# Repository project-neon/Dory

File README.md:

# Dory
3rd Sumo Robot for Project Neon. After Zumo and Nemo, comes Dory.

Repositório de desenvolvimento para a Dory em 2022.

Usamos o fluxo de trabalho apresentado [aqui pelo Gamen](https://github.com/project-neon/codestyleguide/blob/master/git.md). Também está apresentado no [github flow](https://docs.github.com/pt/get-started/quickstart/github-flow). O resumo seria este:

## Arquivos

  Neste repositório temos os principais arquivos que usamos para os 3 capítulos, Eletrônica, Mecânica e Software. Segue abaixo uma lista do que temos em cada uma das pastas:

  ### Electronics
    Na parte eletrônica, utilizamos o programa Kicad que é open source e permite a criação e edição de PCBs.
    Caso queira editar ou vizualizar o projeto, clone o diretório "Eletronics", pois nele está contido o esquemático 
    no formato PDF e sch,  a PCB no formato pcb e os arquivos pro e plr próprios do Kicad.
    
  ### Mechanics
    Na pasta da mecânica, há arquivos no formato step e stl para que possam ser utilizados para visualização 
    e manufatura 3D, juntamente com os arquivos pdf dos desenhos técnicos para melhor compreensão do projeto
    
  ### Software
    Nesta pasta deixamos todos os arquivos que formam o código do robô. Então .ino e .h são os principais arquivos.
    Usamos os .h's para segmentar o código e não ser um único bloco enorme, dividindo eles de acordo com sua funcionalidade.
    O .ino é onde fica a base de todo o código, como o setup() e o loop(). Temos os códigos de testes e o código autonomous
    que usamos durante as lutas oficiais.

## Fluxo Git
- Quando for acrescentar uma feature (um comportamento novo para o robô), crie uma brancha chamada `feat/nome-da-feature`
- Quando for corrir algum bug no código, crie uma brancha chamada `fix/nome-do-fix`
- Quando for adicionar novos arquivos na mecância ou eletrônica, crie uma brancha chamada `update/eletronics-<data>` ou `update/mechanis-<data>`, exemplo: `update/eletronics-01-04-2023`
- A partir da main: `git checkout -b nome-da-branch`, ex: `git checkout -b feat/novos-testes`

## Na hora de fazer o commit
- Nomeie o seu commit primeiro dizendo o que foi feito, ex: `fix: `, `feat: ` ou `update: `
- Você pode adicionar no assunto (comentário) ou na mensagem do commit também onde que a mudança foi feita.
- `git push`

Para saber mais de commits, você pode acessar esse [link](https://www.freecodecamp.org/news/how-to-write-better-git-commit-messages/)

## Na hora de fazer o merge
- Depois de subir o commit, crie um PR (Pull Request) e peça pro resto do pessoal da equipe dar uma conferida antes de ser aprovado

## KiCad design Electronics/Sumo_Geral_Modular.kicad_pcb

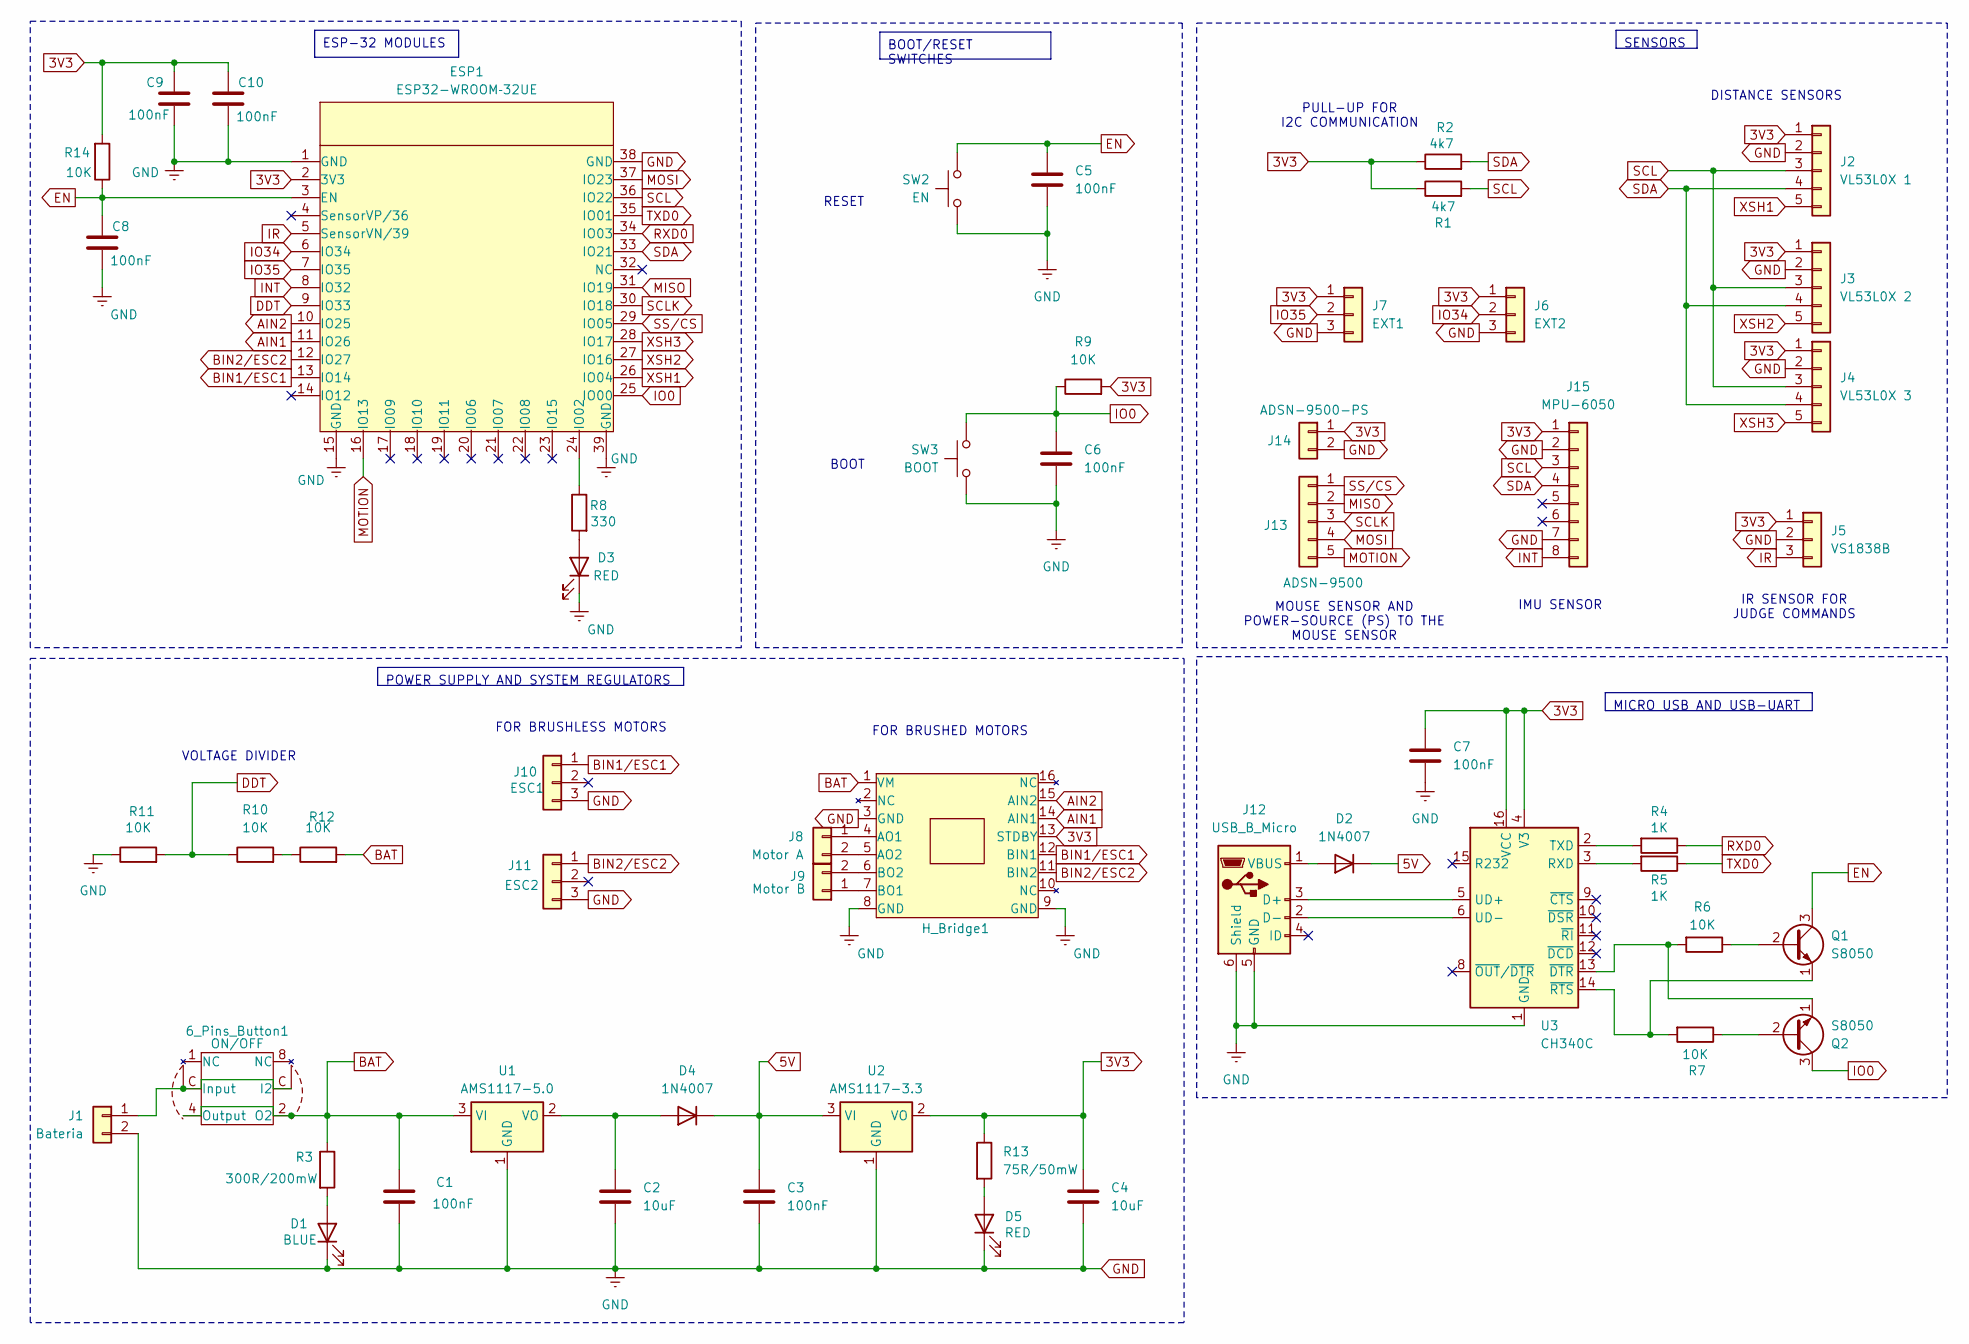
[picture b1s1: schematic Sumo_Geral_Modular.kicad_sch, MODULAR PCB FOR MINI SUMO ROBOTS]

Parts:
6_Pins_Button1: ON/OFF; Push_Button_6_pins
C1, C3, C5, C6, C7, C8, C9, C10: 100nF; C_0603_1608Metric
C2, C4: 10uF; C_0603_1608Metric
D1: BLUE; LED_0603_1608Metric
D2, D4: 1N4007; D_0603_1608Metric
D3, D5: RED; LED_0603_1608Metric
ESP1: ESP32-WROOM­32UE; ESP32-WROOM-32
H_Bridge1: H_Bridge_with_headers
J1: Bateria; JST_PH_B2B-PH-K_1x02_P2.00mm_Vertical
J2: VL53L0X 1; JST_XH_B5B-XH-A_1x05_P2.50mm_Vertical
J3: VL53L0X 2; JST_XH_B5B-XH-A_1x05_P2.50mm_Vertical
J4: VL53L0X 3; JST_XH_B5B-XH-A_1x05_P2.50mm_Vertical
J5: VS1838B; PinHeader_1x03_P2.00mm_Vertical
J6: EXT2; PinHeader_1x03_P2.00mm_Vertical
J7: EXT1; PinHeader_1x03_P2.00mm_Vertical
J8: Motor A; JST_XH_B2B-XH-A_1x02_P2.50mm_Vertical
J9: Motor B; JST_XH_B2B-XH-A_1x02_P2.50mm_Vertical
J10: ESC1; JST_XH_B3B-XH-A_1x03_P2.50mm_Vertical
J11: ESC2; JST_XH_B3B-XH-A_1x03_P2.50mm_Vertical
J12: USB_B_Micro; USB_Micro-B_Amphenol_10118194_Horizontal
J13: ADSN-9500; JST_XH_S5B-XH-A_1x05_P2.50mm_Horizontal
J14: ADSN-9500-PS; JST_XH_S2B-XH-A_1x02_P2.50mm_Horizontal
J15: MPU-6050; PinSocket_1x08_P2.54mm_Vertical
Q1, Q2: S8050; SOT-23
R1, R2: 4k7; R_0603_1608Metric
R3: 300R/200mW; R_0603_1608Metric
R4, R5: 1K; R_0603_1608Metric
R6, R7, R9, R11, R12, R14: 10K; R_0603_1608Metric
R8: 330; R_0603_1608Metric
R10: 10K; C_0603_1608Metric
R13: 75R/50mW; R_0603_1608Metric
SW2: EN; SW_SPST_TL3305C
SW3: BOOT; SW_SPST_TL3305C
U1: AMS1117-5.0; SOT-223-3_TabPin2
U2: AMS1117-3.3; SOT-223-3_TabPin2
U3: CH340C; SOIC-16_3.9x9.9mm_P1.27mm

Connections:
3V3: C4.1, C7.1, C9.1, C10.1, ESP1.2 (3V3), H_Bridge1.13 (STDBY), J2.1, J3.1, J4.1, J5.1, J6.1, J7.1, J14.1, J15.1, R1.1, R2.1, R9.2, R13.1, R14.2, U2.2 (VO), U3.4 (V3), U3.16 (VCC)
5V: C3.1, D2.1 (K), D4.1 (K), U2.3 (VI)
AIN1: ESP1.11 (IO26), H_Bridge1.14 (AIN1)
AIN2: ESP1.10 (IO25), H_Bridge1.15 (AIN2)
BAT: 6_Pins_Button1.2 (O2), 6_Pins_Button1.4 (Output), C1.1, H_Bridge1.1 (VM), R3.1, R12.2, U1.3 (VI)
BIN1/ESC1: ESP1.13 (IO14), H_Bridge1.12 (BIN1), J10.1
BIN2/ESC2: ESP1.12 (IO27), H_Bridge1.11 (BIN2), J11.1
DDT: ESP1.9 (IO33), R10.1, R11.2
EN: C5.2, C8.1, ESP1.3 (EN), Q1.3 (C), R14.1, SW2.1
GND: C1.2, C2.2, C3.2, C4.2, C5.1, C6.2, C7.2, C8.2, C9.2, C10.2, D1.1 (K), D3.1 (K), D5.1 (K), ESP1.1 (GND), ESP1.15 (GND), ESP1.38 (GND), ESP1.39 (GND), H_Bridge1.3 (GND), H_Bridge1.8 (GND), H_Bridge1.9 (GND), J1.2, J2.2, J3.2, J4.2, J5.2, J6.3, J7.3, J10.3, J11.3, J12.5 (GND), J12.6 (Shield), J14.2, J15.2, J15.7, R11.1, SW2.2, SW3.2, U1.1 (GND), U2.1 (GND), U3.1 (GND)
INT: ESP1.8 (IO32), J15.8
IO0: C6.1, ESP1.25 (IO00), Q2.3 (C), R9.1, SW3.1
IO34: ESP1.6 (IO34), J6.2
IO35: ESP1.7 (IO35), J7.2
IR: ESP1.5 (SensorVN/39), J5.3
MISO: ESP1.31 (IO19), J13.2
MOSI: ESP1.37 (IO23), J13.4
MOTION: ESP1.16 (IO13), J13.5
unnamed: 6_Pins_Button1.C (I2), J1.1
unnamed: D1.2 (A), R3.2
unnamed: D2.2 (A), J12.1 (VBUS)
unnamed: D3.2 (A), R8.2
unnamed: C2.1, D4.2 (A), U1.2 (VO)
unnamed: D5.2 (A), R13.2
unnamed: ESP1.24 (IO02), R8.1
unnamed: H_Bridge1.4 (AO1), J8.1
unnamed: H_Bridge1.5 (AO2), J8.2
unnamed: H_Bridge1.7 (BO1), J9.1
unnamed: H_Bridge1.6 (BO2), J9.2
unnamed: J12.3 (D+), U3.5 (UD+)
unnamed: J12.2 (D-), U3.6 (UD-)
unnamed: Q1.2 (B), R6.1
unnamed: Q1.1 (E), R7.2, U3.14 (~RTS)
unnamed: Q2.2 (B), R7.1
unnamed: Q2.1 (E), R6.2, U3.13 (~DTR)
unnamed: R10.2, R12.1
unnamed: R5.2, U3.3 (RXD)
unnamed: R4.2, U3.2 (TXD)
RXD0: ESP1.34 (IO03), R4.1
SCL: ESP1.36 (IO22), J2.3, J3.3, J4.3, J15.3, R1.2
SCLK: ESP1.30 (IO18), J13.3
SDA: ESP1.33 (IO21), J2.4, J3.4, J4.4, J15.4, R2.2
SS/CS: ESP1.29 (IO05), J13.1
TXD0: ESP1.35 (IO01), R5.1
XSH1: ESP1.26 (IO04), J2.5
XSH2: ESP1.27 (IO16), J3.5
XSH3: ESP1.28 (IO17), J4.5

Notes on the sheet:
SENSORS
ESP-32 MODULES
BOOT/RESET SWITCHES
MICRO USB AND USB-UART
POWER SUPPLY AND SYSTEM REGULATORS
MOUSE SENSOR AND POWER-SOURCE (PS) TO THE MOUSE SENSOR
FOR BRUSHLESS MOTORS
VOLTAGE DIVIDER
FOR BRUSHED MOTORS
PULL-UP FOR I2C COMMUNICATION
IR SENSOR FOR JUDGE COMMANDS
IMU SENSOR
DISTANCE SENSORS
BOOT
RESET

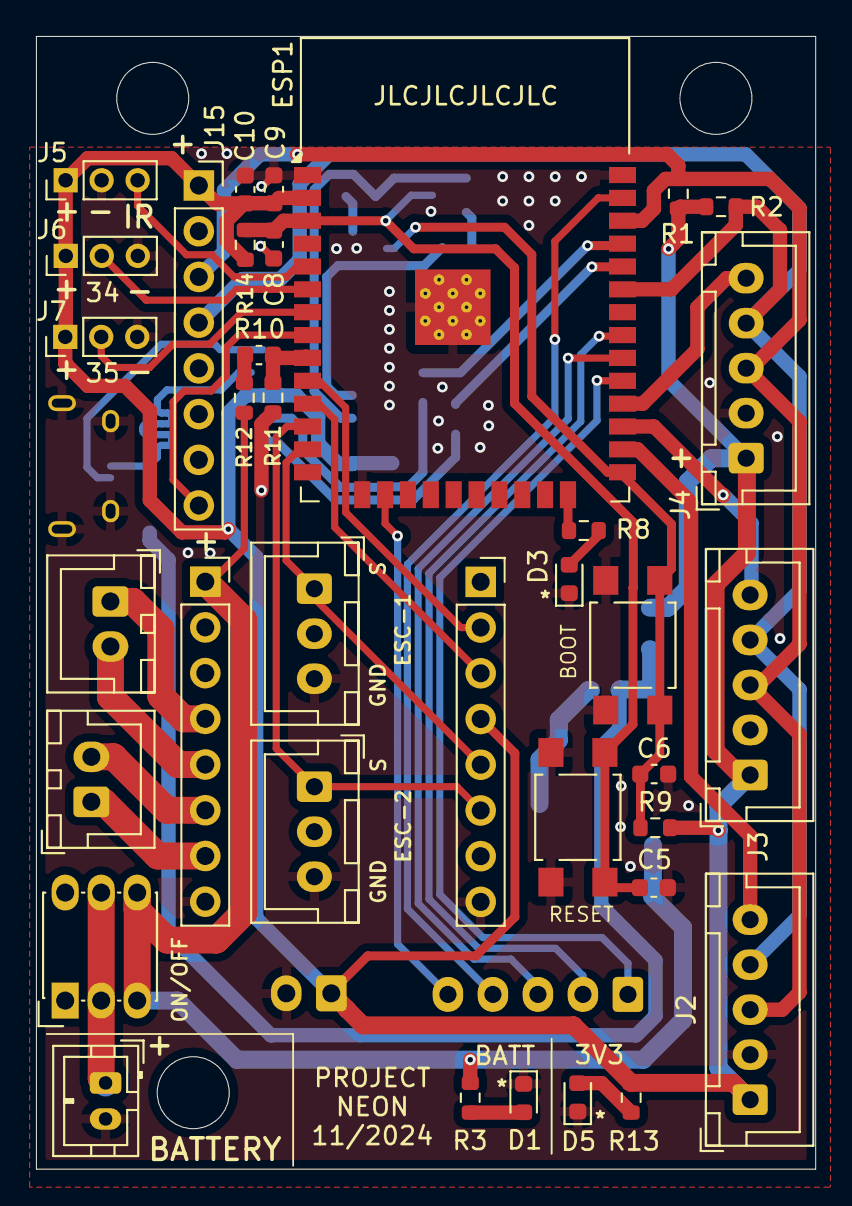
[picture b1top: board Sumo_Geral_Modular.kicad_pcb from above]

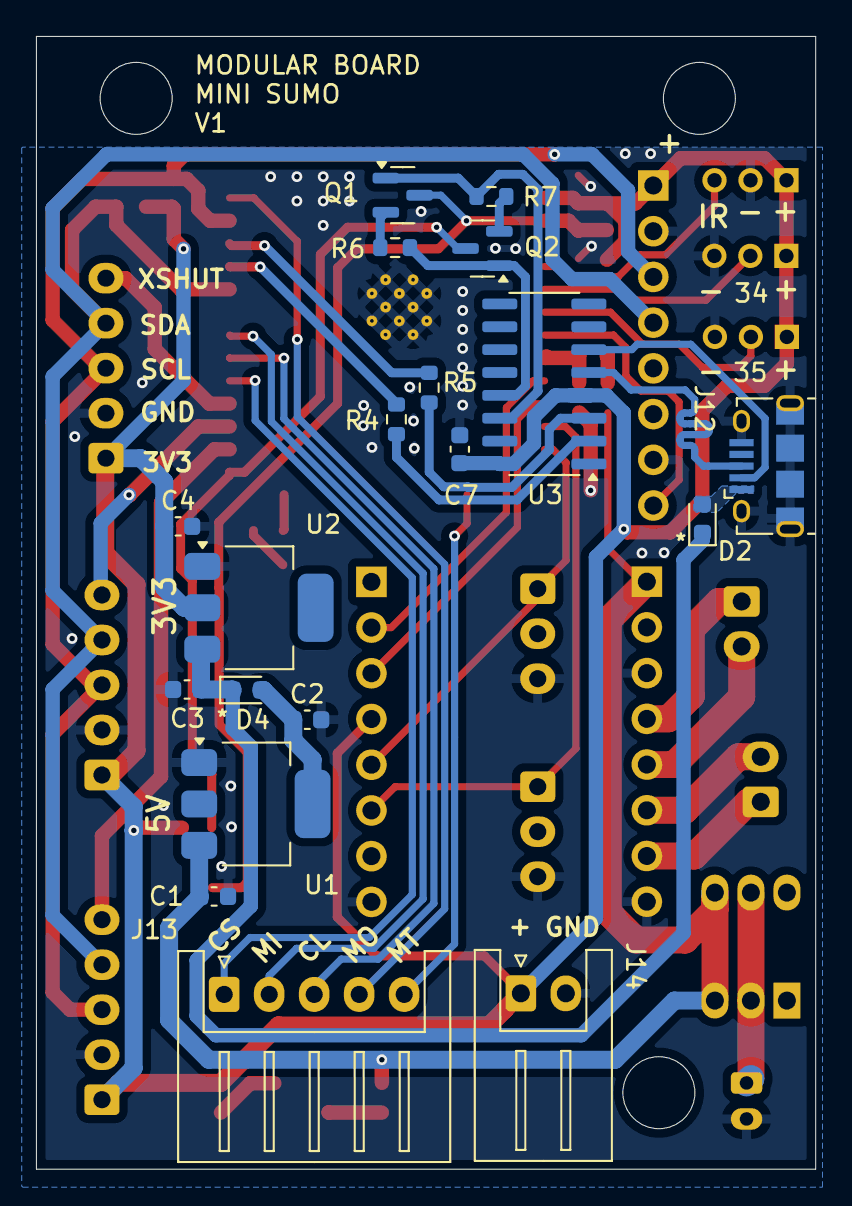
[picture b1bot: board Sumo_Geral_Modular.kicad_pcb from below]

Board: 2 copper layers, 43.3 x 62.9 mm, 54 parts (19 on the bottom side), 47 nets.

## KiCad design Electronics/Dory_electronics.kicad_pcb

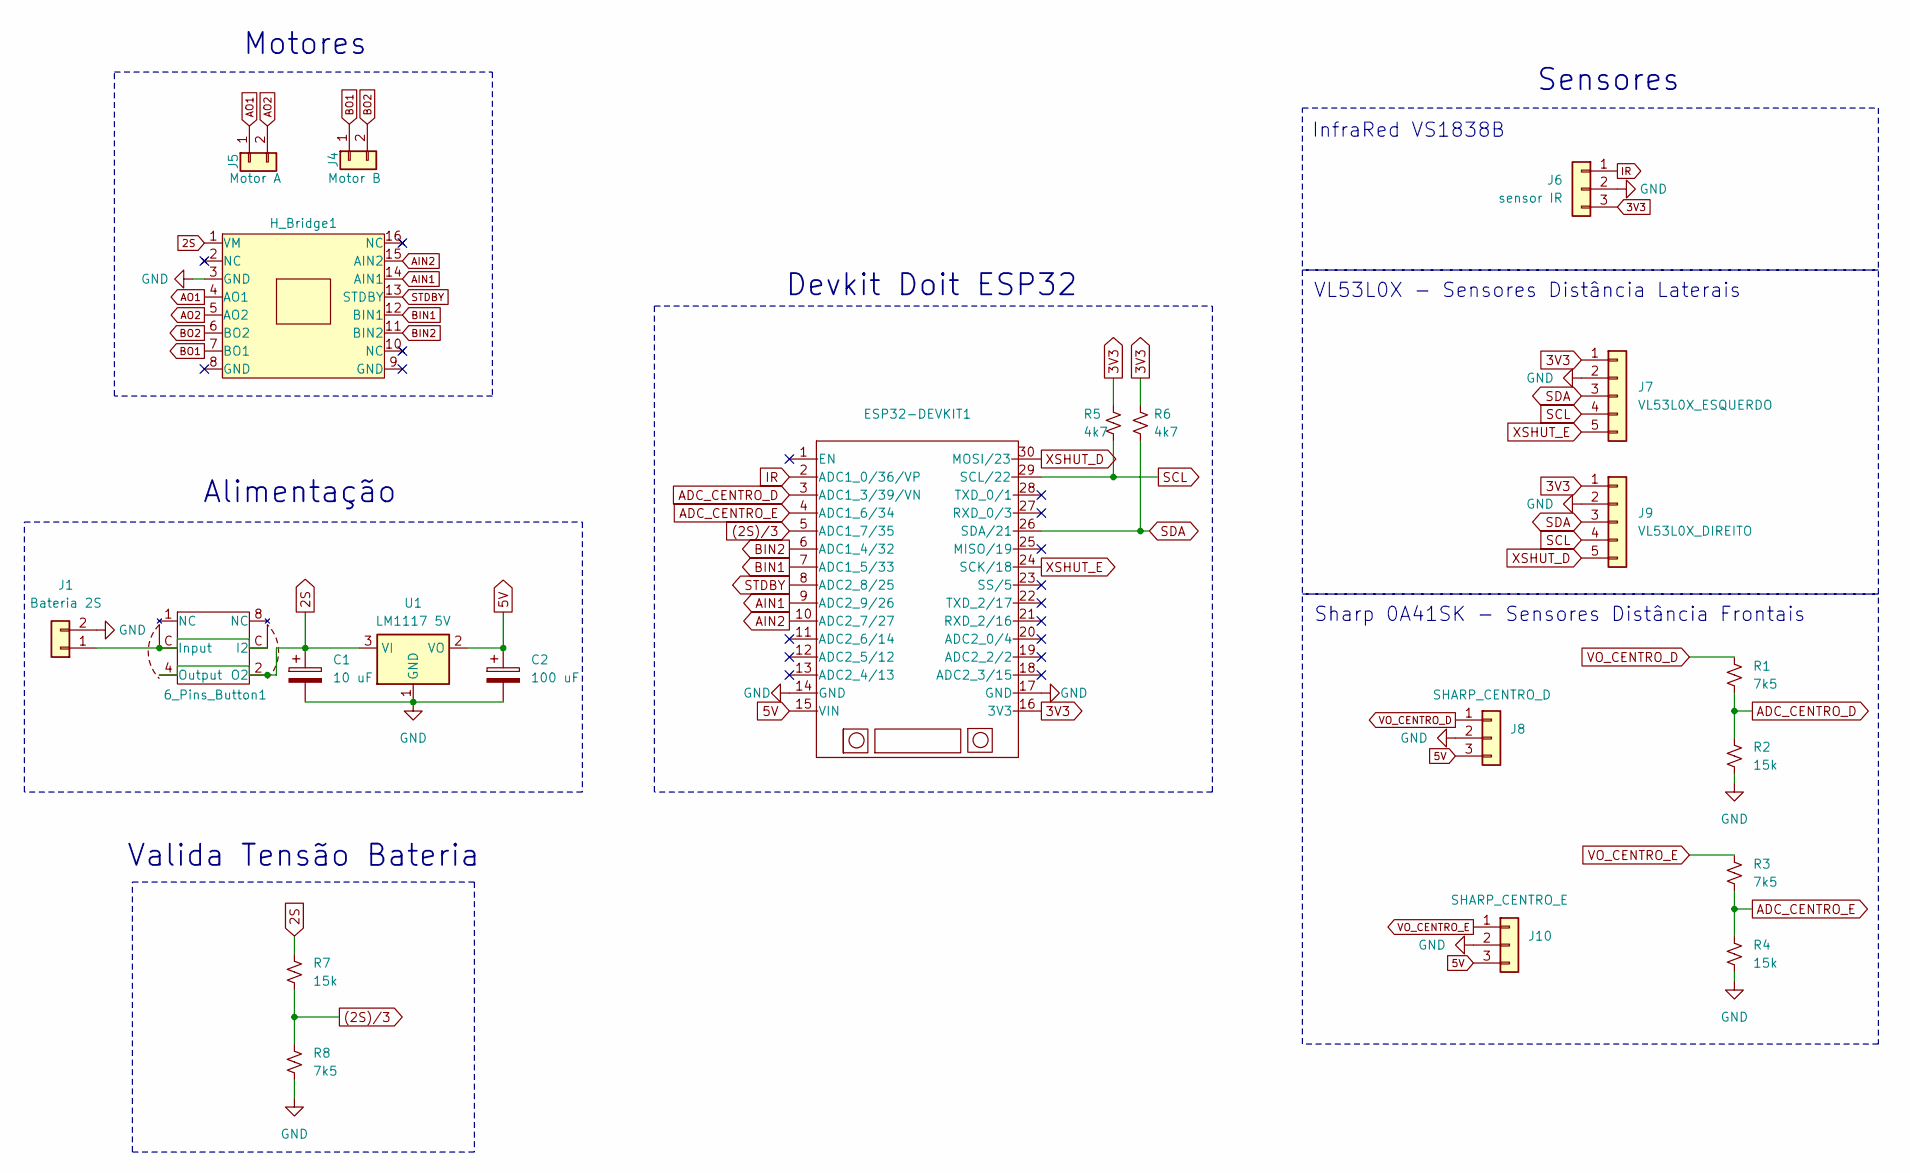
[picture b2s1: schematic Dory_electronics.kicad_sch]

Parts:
6_Pins_Button1: Push_Button_6_pins
C1: 10 uF; CP_Radial_D5.0mm_P2.50mm
C2: 100 uF; CP_Radial_D6.3mm_P2.50mm
ESP32-DEVKIT1: esp32_with_headers
H_Bridge1: H_Bridge_with_headers
J1: Bateria 2S; JST_PH_B2B-PH-K_1x02_P2.00mm_Vertical
J4: Motor B; JST_XH_B2B-XH-A_1x02_P2.50mm_Vertical
J5: Motor A; JST_XH_B2B-XH-A_1x02_P2.50mm_Vertical
J6: sensor IR; PinHeader_1x03_P2.54mm_Vertical
J7: VL53L0X_ESQUERDO; JST_XH_B5B-XH-A_1x05_P2.50mm_Vertical
J8: SHARP_CENTRO_D; PinSocket_1x03_P2.54mm_Vertical
J9: VL53L0X_DIREITO; JST_XH_B5B-XH-A_1x05_P2.50mm_Vertical
J10: SHARP_CENTRO_E; PinSocket_1x03_P2.54mm_Vertical
R1, R3, R8: 7k5; R_0805_2012Metric
R2, R4, R7: 15k; R_0805_2012Metric
R5, R6: 4k7; R_Axial_DIN0207_L6.3mm_D2.5mm_P10.16mm_Horizontal
U1: LM1117 5V; TO-220-3_Vertical

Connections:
2S: 6_Pins_Button1.2 (O2), 6_Pins_Button1.4 (Output), C1.1, H_Bridge1.1 (VM), R7.1, U1.3 (VI)
3V3: ESP32-DEVKIT1.16 (3V3), J6.3, J7.1, J9.1, R5.2, R6.1
5V: C2.1, ESP32-DEVKIT1.15 (VIN), J8.3, J10.3, U1.2 (VO)
(2S)/3: ESP32-DEVKIT1.5 (ADC1_7/35), R7.2, R8.1
ADC_CENTRO_D: ESP32-DEVKIT1.3 (ADC1_3/39/VN), R1.2, R2.1
ADC_CENTRO_E: ESP32-DEVKIT1.4 (ADC1_6/34), R3.2, R4.1
AIN1: ESP32-DEVKIT1.9 (ADC2_9/26), H_Bridge1.14 (AIN1)
AIN2: ESP32-DEVKIT1.10 (ADC2_7/27), H_Bridge1.15 (AIN2)
AO1: H_Bridge1.4 (AO1), J5.1
AO2: H_Bridge1.5 (AO2), J5.2
BIN1: ESP32-DEVKIT1.7 (ADC1_5/33), H_Bridge1.12 (BIN1)
BIN2: ESP32-DEVKIT1.6 (ADC1_4/32), H_Bridge1.11 (BIN2)
BO1: H_Bridge1.7 (BO1), J4.1
BO2: H_Bridge1.6 (BO2), J4.2
GND: C1.2, C2.2, ESP32-DEVKIT1.14 (GND), ESP32-DEVKIT1.17 (GND), H_Bridge1.3 (GND), J1.2, J6.2, J7.2, J8.2, J9.2, J10.2, R2.2, R4.2, R8.2, U1.1 (GND)
IR: ESP32-DEVKIT1.2 (ADC1_0/36/VP), J6.1
unnamed: 6_Pins_Button1.C (I2), J1.1
SCL: ESP32-DEVKIT1.29 (SCL/22), J7.4, J9.4, R5.1
SDA: ESP32-DEVKIT1.26 (SDA/21), J7.3, J9.3, R6.2
STDBY: ESP32-DEVKIT1.8 (ADC2_8/25), H_Bridge1.13 (STDBY)
VO_CENTRO_D: J8.1, R1.1
VO_CENTRO_E: J10.1, R3.1
XSHUT_D: ESP32-DEVKIT1.30 (MOSI/23), J9.5
XSHUT_E: ESP32-DEVKIT1.24 (SCK/18), J7.5

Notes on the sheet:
Sensores
VL53L0X - Sensores Distância Laterais
Motores
Sharp 0A41SK - Sensores Distância Frontais
Valida Tensão Bateria
InfraRed VS1838B
Alimentação
Devkit Doit ESP32

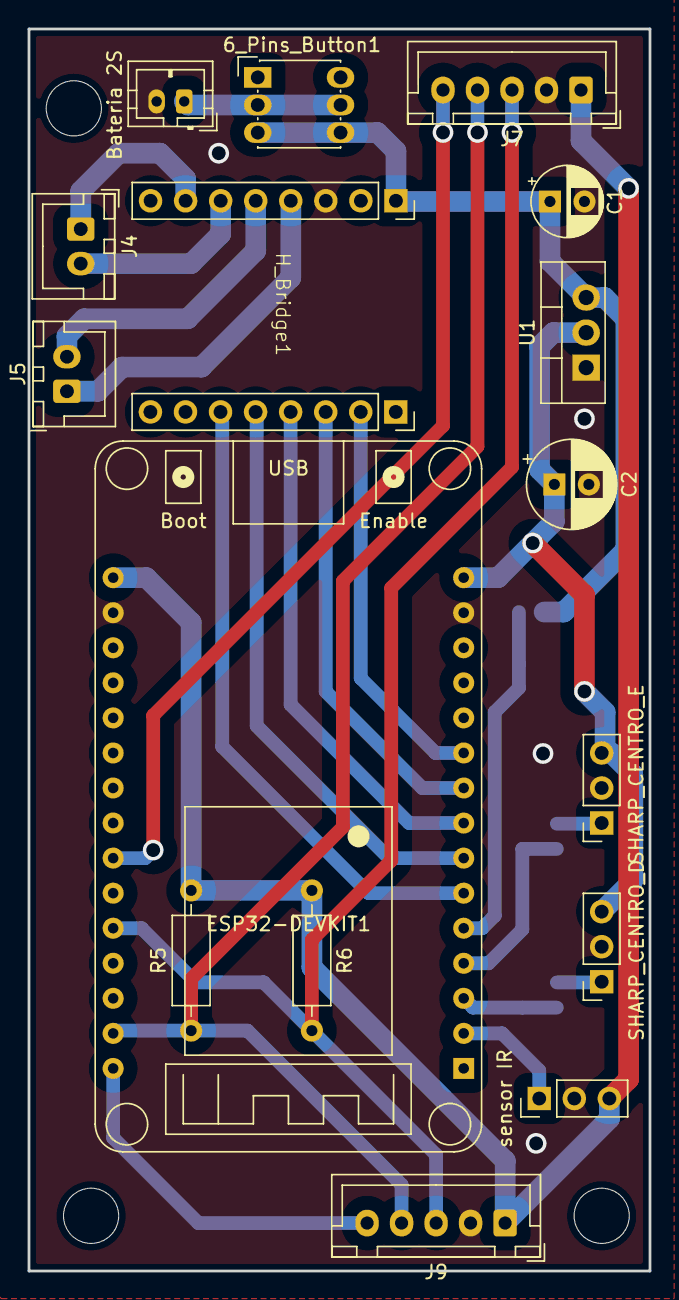
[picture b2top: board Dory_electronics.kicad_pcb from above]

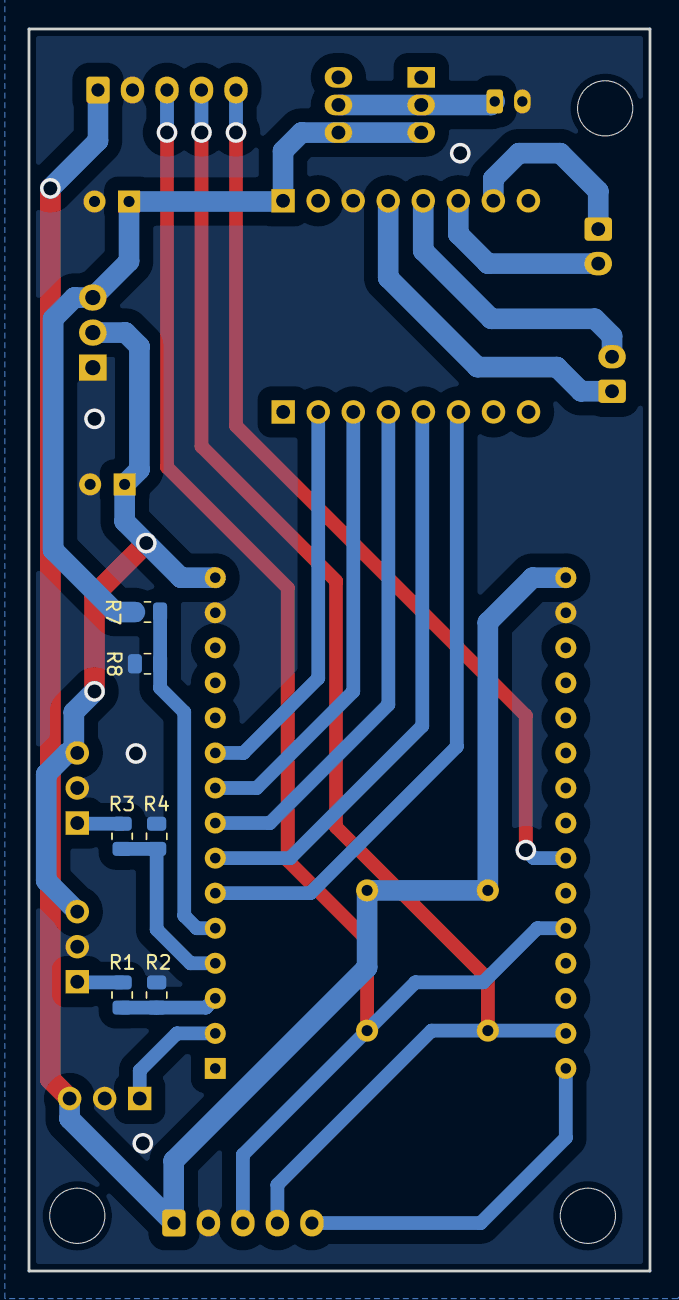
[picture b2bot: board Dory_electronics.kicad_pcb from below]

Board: 2 copper layers, 45.0 x 90.0 mm, 22 parts (6 on the bottom side), 24 nets.

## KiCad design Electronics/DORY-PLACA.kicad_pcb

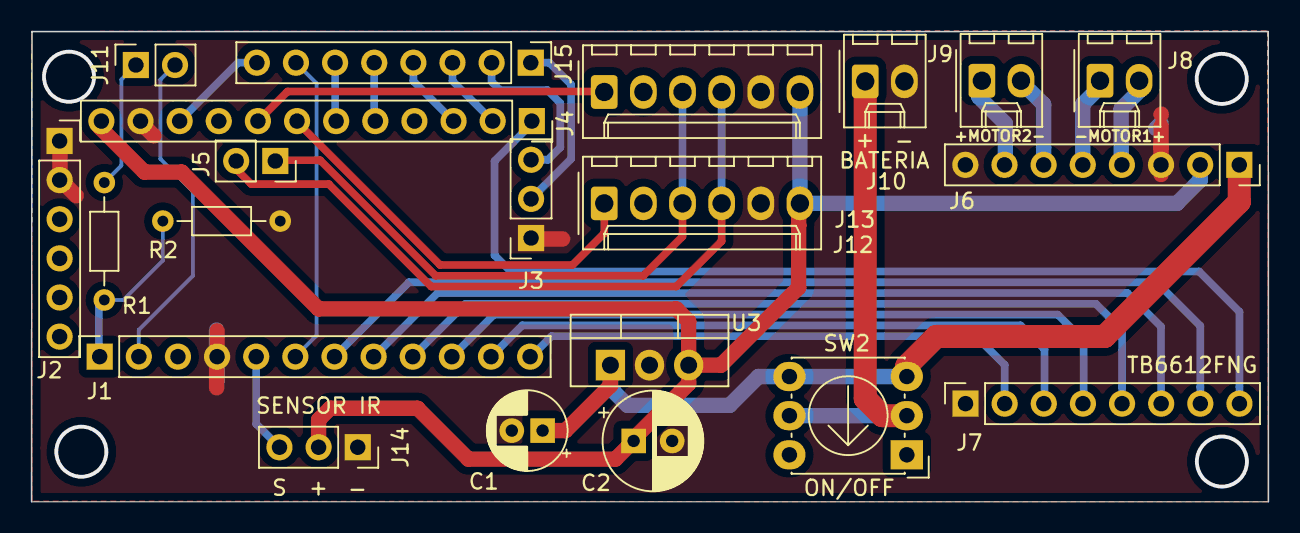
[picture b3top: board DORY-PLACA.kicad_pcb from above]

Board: 2 copper layers, 80.3 x 30.5 mm, 21 parts (0 on the bottom side), 32 nets.

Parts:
C1: 10uF; CP_Radial_D5.0mm_P2.00mm
C2: 100uF; CP_Radial_D6.3mm_P2.50mm
J1: Left Side_ Arduino Pro mini; PinSocket_1x12_P2.54mm_Vertical
J2: Top Side_Promini Pro; PinSocket_1x06_P2.54mm_Vertical
J3, J14: Conn_01x03_Female; PinSocket_1x03_P2.54mm_Vertical
J4: Right Side_ Arduino Pro mini; PinSocket_1x12_P2.54mm_Vertical
J5: A4 and A5; PinSocket_1x02_P2.54mm_Vertical
J6: ESQUERDO-PONTE-H; PinSocket_1x08_P2.54mm_Vertical
J7: DIREITO-PONTE-H; PinSocket_1x08_P2.54mm_Vertical
J8: Motor1; Molex_KK-254_AE-6410-02A_1x02_P2.54mm_Vertical
J9: Motor2; Molex_KK-254_AE-6410-02A_1x02_P2.54mm_Vertical
J10: Conn_01x02_Male; Molex_KK-254_AE-6410-02A_1x02_P2.54mm_Vertical
J11: BLUETOOTH; PinSocket_1x02_P2.54mm_Vertical
J12, J13: Conn_01x06_Male; Molex_KK-254_AE-6410-06A_1x06_P2.54mm_Vertical
J15: Conn_01x06_Male; PinHeader_1x08_P2.54mm_Vertical
R1: 1kΩ; R_Axial_DIN0204_L3.6mm_D1.6mm_P7.62mm_Horizontal
R2: 2kΩ; R_Axial_DIN0204_L3.6mm_D1.6mm_P7.62mm_Horizontal
SW2: SW_Push; Nidec_Copal_SH-7010C
U3: LM7805_TO220; TO-220-3_Vertical

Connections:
+5V: C2.1, J4.12, J6.2, J12.6, J13.6, J14.2, U3.3
+BAT: C1.1, J6.1, SW2.2, U3.1
A0: J4.5, J15.5
A1: J4.6, J15.6
A6: J3.2, J15.1
A7: J3.3, J15.2
AIN1: J1.8, J7.6
AIN2: J1.7, J7.7
AO1: J6.4, J8.2
AO2: J6.5, J8.1
BIN1: J1.10, J7.4
BIN2: J1.11, J7.3
BO1: J6.7, J9.1
BO2: J6.6, J9.2
D3: J1.6, J15.7
D11: J4.2, J15.3
D12: J4.3, J15.4
GND: C1.2, C2.2, J1.4, J2.1, J2.2, J3.1, J4.11, J6.3, J6.8, J7.1, J10.2, J12.5, J13.5, J14.1, R2.2, U3.2
IR_SENSOR: J1.5, J14.3
unnamed: J10.1, SW2.1
unnamed: J11.1, R1.1
PWMA: J4.1, J7.8
PWMB: J1.12, J7.2
RESET: J1.3, J4.10, J15.8
SCL: J5.2, J12.4, J13.4
SDA: J5.1, J12.3, J13.3
STBY: J1.9, J7.5
TXD: R1.2, R2.1
TXO: J1.1, J2.5
VCC: J2.3, J4.9
XSHUT1: J4.8, J13.1
XSHUT2: J4.7, J12.1

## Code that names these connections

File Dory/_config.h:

#include <Arduino.h>

//Motor A LADO ESQUERDO
#define PWMA 10 //Speed control
#define AIN1 5  //Direction
#define AIN2 4  //Direction

//Motor B LADO DIREITO
#define PWMB 9 //Speed control
#define BIN1 7 //Direction
#define BIN2 8 //Direction

#define STBY 6 //Stand-by

// Motors config (H-Bridge)
#define MOTOR_ABS_MAX 255

//Sensor IR
#define RECV_PIN 2 

//Sensores de distância
#define sharp_E A3 //Esquerda
#define sharp_D A2 //Direita

//LED
#define PIN_REDLED 13

//LED RGB

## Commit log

2022-08-29 Criação do cronograma
2022-08-29 Atualização do Cronogram
2022-08-29 Correção Cronograma
2023-03-18 add: Electronics and Mechanics files
2023-03-20 add: info about each folder on README
2023-03-26 fix: organizing Electronics and Mechanical folders
2023-03-26 fix: organizing Software folder
2023-12-31 feat: start ESP32 compatible code
2024-01-22 feat: create a new strategy for Dory
2024-01-23 fix: change on Simple Strategy
2024-01-23 fix: strategy errors
2024-01-30 fix: motors errors
2024-02-06 fix: engine failures
2024-02-23 fix: motors corrections
2024-02-28 fix:engine speed
2024-02-28 fix: delay on motors
2024-04-20 docs: add new comments
2024-04-20 chore: update electronics files
2024-05-15 chore: update Mechanics files
2024-06-15 add: Dory's Schematic
2024-06-15 chore[Electronics]: add h bridge and IR
2024-06-20 fix: organize Electronics folder
2024-06-20 chore: organize schematic and add gitignore
2024-06-21 feat: add VL530X
2024-06-29 fix(Electronics): remove center vl53l0x from sch
2024-07-02 chore: revision of the PCB
2024-07-17 chore: update Electronics
2024-08-31 chore: add footprints to schematic
2024-09-03 chore(Electronics): organize and finish schematic
2024-09-07 chore: update schematic and PCB
2024-09-13 chore: redo paths to homemade pcb
2024-09-14 chore: change .step to be above pcb
2024-09-14 chore: update esp32 lib sym and footprint
2024-09-15 chore: Add/Update 3D models on PCB
2024-09-28 chore: update PCB and create BOM file
2024-09-29 chore(Electronics): update .step
2024-10-05 chore: add VL53L0X to code
2024-10-09 chore: Update Electronics and Software files
2024-10-10 fix: fix IR judge controller buttons
2025-09-08 docs(Mechanics): add drawings
2025-09-08 docs(Electronics): add modular PCB
